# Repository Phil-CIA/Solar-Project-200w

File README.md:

# Solar Project 200W

Solar Project 200W is a prototype-first hardware and firmware effort for a 200W-class solar charging system built around a 4S LiFePO4 battery domain.

## What this repository is for

- Designing and validating a safe MPPT charger path
- Defining control, telemetry, and protection behavior
- Tracking design decisions, handoffs, and bring-up evidence

## Rev2 preparation

Phil selected **retain LM51772 for Rev2**. Open `hardware\kicad\solar-project\Solar Project Rev2.kicad_pro` for new Rev2 work; its schematic/PCB are a metadata-only copy of the reconciled Rev1 development source at `32243b5` (tag `rev2-development-baseline-2026-11-09`), not an implemented or qualified redesign and not for fabrication. See the [revision index](hardware/kicad/solar-project/REVISION-INDEX.md), [consolidation/change register](docs/rev-two-consolidation.md), and current [handoff](HANDOFF.md) for source identity, bench evidence and unresolved work. The controller-comparison requirement in [#20](https://github.com/Phil-CIA/Solar-Project-200w/issues/20) remains open; no BQ25756 evaluation or purchase is requested.

## Rev 1 manufactured baseline

- Only Rev 0 and Rev 1 have been manufactured; Rev 2 is a copied development starting set. Rev 1 is the current production revision. The production release at `C:\Users\user\OneDrive\JLCPCB files\Solar Charger\Rev 1` is authoritative for board identity, manufacturing and board-specific tests. Repository copies support continued development; the schematic, project and BOM differences are described in the board notes.
- Rev 1 is assembled; the supplied manufacturing package and both-side photos are recorded in [board notes](docs/rev-one-board-notes.md).
- Retain the Rev 1 [development tracker](https://github.com/Phil-CIA/Solar-Project-200w/issues/1) and [working plan](docs/rev-one-closure-plan-2026-09-16.md#6-assembled-board-execution-and-issue-1-closure) as qualification references. Later bench findings and current next steps are linked from the handoff; old unpowered checkpoints are not the current board state.
- This is a hobby prototype: keep useful notes and relevant checks, not a formal lab dossier. Assembly does not establish working charging or full-power performance.
- Rev 1 STM32G473 bring-up firmware through `ff89791` is already on `main`; see [firmware notes](firmware/README.md). That is development progress, not proof of board compatibility or a passing powered test.

## System baseline

- PV class: 2x100W panels in parallel (DEC-051)
- Battery class: 12.8V LiFePO4 (4S)
- Rev 1 design targets: 125 W continuous output, 150 W maximum PV operating power, 8-10 A nominal charging, approximately 12 A hardware protection pending verification

## Project structure

- [docs/](docs/): requirements, architecture, decisions, test plans, phase reviews
- [hardware/](hardware/): KiCad files, MPPT notes, wiring maps, implementation checklists
- [firmware/](firmware/): firmware workspace and bring-up software notes

## Start here

1. [HANDOFF.md](HANDOFF.md) - current checkpoint and next step
2. [docs/rev-one-board-notes.md](docs/rev-one-board-notes.md) - working board baseline and known differences
3. [docs/README.md](docs/README.md) - engineering references
4. [docs/decisions-log.md](docs/decisions-log.md) - retained design decisions
5. [SOLAR_HANDOFF_2026-09-19.md](SOLAR_HANDOFF_2026-09-19.md) and [SOLAR_HANDOFF_2026-09-18.md](SOLAR_HANDOFF_2026-09-18.md) for the historical Rev 1 fabrication closeout
6. [hardware/kicad/solar-project/REVISION-INDEX.md](hardware/kicad/solar-project/REVISION-INDEX.md) for KiCad source-of-truth rules

## Simulation workflow

The PV switch gate-drive concept should be verified with SPICE as part of the normal review loop. The project-local LTspice assets are in [hardware/kicad/solar-project/spice](hardware/kicad/solar-project/spice), including the schematic draft [hardware/kicad/solar-project/spice/pv_switch_gate_drive.asc](hardware/kicad/solar-project/spice/pv_switch_gate_drive.asc) and the launcher [hardware/kicad/solar-project/spice/run_ltspice_pv_gate_drive.cmd](hardware/kicad/solar-project/spice/run_ltspice_pv_gate_drive.cmd).

A provisional LTspice integration harness is also present at [hardware/kicad/solar-project/spice/90_system_integration_harness_ltspice.cir](hardware/kicad/solar-project/spice/90_system_integration_harness_ltspice.cir). It is a simplified, staged model of the PV input, buck power stage, and battery boundary. The current run converged to about 13.64 V at the output node and 13.98 V at the battery bus at 4 ms, which is consistent with a basic charging path but still not hardware-validated.

Earlier simulation identified a gate-drive margin problem in the arrangement it modeled. That historical result is not a measured failure of the assembled Rev 1 U14/Q5/Q6 protection circuit; confirm the topology against the Rev 1 production release and use matching low-energy checks before drawing that conclusion.

## Safety notice

This project includes high-current DC power electronics and planned AC-domain integration.
Use staged, current-limited bring-up and treat all safety checks as mandatory gates.

## Session continuity

- [HANDOFF.md](HANDOFF.md)
- [NEXT_CHAT_PROMPT.md](NEXT_CHAT_PROMPT.md)

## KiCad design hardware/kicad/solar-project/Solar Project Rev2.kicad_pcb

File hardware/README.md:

# Hardware

Store hardware development assets here.

Suggested structure:
- `schematics/`
- `pcb/`
- `bom/`
- `manufacturing/`
- `validation/`

Add tool/version notes and board revision history as the project evolves.

## Phase 1 Kickoff Artifacts

- `mppt/block-diagram.md`
- `mppt/schematic-exploration-checklist.md`
- `mppt/interface-assumptions.md`
- `mppt/schematic-notes.md`
- `mppt/net-plan.md`
- `mppt/component-shortlist-template.md`
- `mppt/kicad-implementation-checklist.md`
- `mppt/envelope-decision-worksheet.md`
- `mppt/decision-update-template.md`
- `mppt/buck-topology-notes.md`
- `mppt/github-reference-notes.md`
- `mppt/buck-symbol-placement-checklist.md`
- `mppt/pv-input-stage.md`
- `mppt/pv-input-wiring-map.md`
- `mppt/buck-power-stage-wiring-map.md`
- `mppt/sheet2-component-picks.md`

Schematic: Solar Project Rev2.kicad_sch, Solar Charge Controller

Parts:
10mm1, 10mm2: 10mm LOGO
C1, C8, C12, C22, C28, C33, C44, C45, C46, C47, C48, C51, C54, C57, C58, C59, C60: 100nF; C_0805; Voltage Rated 100V; Tolerance ±10%; Part CL21B104KCFNNNE; LCSC C28233
C2, C55, C56: 1uF; C_0805; Voltage Rated 50V; Tolerance ±10%; Part CL21B105KBFNNNE; LCSC C28323
C3: 100uF; CP_Radial_D6.3mm_P2.50mm; LCSC C49232871
C7: 2.2uF; C_1206; Voltage Rated 100V; Tolerance ±10%; Part CC1206KKX7R0BB225; LCSC C577211
C9, C13: 2.2nF; C_0805; Voltage Rated 50V; Tolerance ±5%; Part CL21C222JBFNNNE; LCSC C28260
C10: 47pF; C_0805; Voltage Rated 50V; Tolerance ±5%; Part CL21C470JBANNNC; LCSC C14857
C14, C53: 100uF; C_1206; Voltage Rated 6.3V; Tolerance ±20%; Part CL31A107MQHNNNE; JLCPCB ID C45783
C15, C34, C35: 2.2uF; C_1206; Voltage Rated 50V; Tolerance ±10%; Part CL31B225KBHNNNE; LCSC C50254
C18: 560uF; CP_Elec_10x12.6; LCSC C264031
C19, C21, C30, C31: 47uF; CP_Radial_D8.0mm_P3.50mm; LCSC C44606514
C20: 180pF; C_0805; LCSC C1794
C23: 100nF; C_0805; LCSC C28233
C24: 22nF; C_0805; LCSC C1710
C25: 1.5nF; C_0805; LCSC C1590
C26: 33nF; C_0805; LCSC C1738
C27, C29: 22uF; C_0805; Voltage Rated 25V; Tolerance ±20%; Part CL21A226MAQNNNE; LCSC C45783
C49, C50: 33pF; C_0805; Voltage Rated 50V; Tolerance ±5%; Part CC0805JRNPO9BN330; LCSC C1798
C52: 220nF; C_0805; Voltage Rated 50V; Tolerance ±10%; Part CL21B224KBFNNNE; LCSC C5378
C61: DNP; C_0805; Voltage Rated 100V; Tolerance ±10%; Part CL21B104KCFNNNE; not fitted
D1, D5: 1SMA4742A; D_DO-214AC(SMA); Part 1SMA4742A; LCSC C19077480
D2: SMBJ48CA; D_SMB; Part SMBJ48CA; LCSC C151264
D3: USBLC6-2SC6; SOT-23-6; MPN USBLC6-2SC6; Digi-Key_PN 497-5235-1-ND
D4, D6, D7, D10: 1N5819WS; D_SOD-323; Forward Voltage (Vf@If) 600mV@1A; Reverse Voltage (Vr) 40V; Part 1N5819WS; LCSC C191023
D8, D11: WS2812B; LED-SMD_4P-L1.6-W1.5_XL-1615RGBC-WS2812B; LCSC C5349954
D9: Green; D_0805; Forward Voltage (VF) 1.6V~2.6V; Part KT-0805G; LCSC C2297
D12: Yellow; D_0805; Forward Voltage (VF) 1.6V~2.6V; Part KT-0805Y; LCSC C2296
F1, F2: 3522-2; Automotive fuse holder keystone 3522-2_KEY; Part - USA Keystone 3522-2, sourced via Digikey/Mo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
J1, J3: Screw_Terminal_01x02; TerminalBlock_Phoenix_MKDS-1,5-2-5.08_1x02_P5.08mm_Horizont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; LCSC C8439
J2: USB4105-GF-A; GCT_USB4105-GF-A; PARTREV B4; LCSC C3020560
J4: Conn_01x04; PinHeader_1x04_P2.54mm_Vertical_SMD_Pin1Right; LCSC C41417361
J7: Fan; PinHeader_1x03_P2.54mm_Vertical; LCSC C29275
J8: Conn_01x04; PinHeader_1x04_P2.54mm_Vertical
L2: L; L_APV_APH1240; LCSC C49308530
L3: L; L_KOHERelec_MDA7030; LCSC C49333024
M1, M2, M3, M4: CSD18540Q5B; TDSON-8-1; LCSC C86513
Q2, Q3, Q7: 2N7002K; Q_SOT-23; Part 2N7002K; LCSC C22379475
Q4: HSBA0119; PQFN-8-EP_6x5mm_P1.27mm_Generic; LCSC C53244070
Q5, Q6: BSC040N10NS5; TDSON-8-1; LCSC C534334
R1, R2, R32, R38, R67: 100kΩ; R_0805; Overload Voltage (Max) 150V; Tolerance ±1%; Part 0805W8F1003T5E; LCSC C17416
R3, R18: 76.8k; R_0805; LCSC C3000581
R4, R26, R27, R41, R65, R69, R70, R71, R72, R73: 10Ω; R_0805; Overload Voltage (Max) 150V; Tolerance ±1%; Part 0805W8F100JT5E; LCSC C17414
R5, R44, R45: 4.7kΩ; R_0805; Overload Voltage (Max) 150V; Tolerance ±1%; Part 0805W8F4701T5E; LCSC C17673
R6, R19, R34, R36, R47, R48, R53, R54, R55, R56, R57, R58, R59, R82, R86: 10kΩ; R_0805; Overload Voltage (Max) 150V; Tolerance ±1%; Part 0805W8F1002T5E; LCSC C17415
R7, R10, R61: 20kΩ; R_0805; Overload Voltage (Max) 150V; Tolerance ±1%; Part 0805W8F2002T5E; LCSC C17523
R8: 27kΩ; R_0805; Overload Voltage (Max) 150V; Tolerance ±1%; Part 0805W8F2702T5E; LCSC C17547
R9: 180k; R_0805; LCSC C17497
R11, R39: 330Ω; R_0805; Overload Voltage (Max) 150V; Tolerance ±1%; Part 0805W8F3300T5E; LCSC C17650
R12: 6.8kΩ; R_0805; Overload Voltage (Max) 150V; Tolerance ±1%; Part 0805W8F6801T5E; LCSC C17730
R13: 1MΩ; R_0805; Overload Voltage (Max) 150V; Tolerance ±1%; Part 0805W8F1004T5E; LCSC C17514
R14: 330kΩ; R_0805; Overload Voltage (Max) 150V; Tolerance ±1%; Part 0805W8F3303T5E; LCSC C17651
R15: 2kΩ; R_0805; Overload Voltage (Max) 150V; Tolerance ±1%; Part 0805W8F2001T5E; LCSC C17537
R16, R22, R80: .005; RES_2012_SUS- wide 0805; LCSC C2073455
R17, R25: 5.62k; R_0805; LCSC C2933470
R20: 499k; R_0805; LCSC C119857
R21: 102k; R_0805; LCSC C119830
R23: 75kΩ; R_0805; Overload Voltage (Max) 150V; Tolerance ±1%; Part 0805W8F7502T5E; LCSC C17743
R24, R62: 5.1kΩ; R_0805; Overload Voltage (Max) 150V; Tolerance ±1%; Part 0805W8F5101T5E; LCSC C17700
R28: 51.7k; R_0805; LCSC C119851
R29: 20.5k; R_0805; LCSC C119842
R30: 40.2k; R_0805; LCSC C119848
R31: 2.43k; R_0805; LCSC C119853
R33, R49, R63, R64: 0Ω; R_0805; Overload Voltage (Max) 150V; Tolerance ±1%; Part 0805W8F0000T5E; LCSC C17888
R35, R81: 180kΩ; R_0805; Overload Voltage (Max) 150V; Tolerance ±1%; Part 0805W8F1803T5E; LCSC C17497
R37, R66: 2.2MΩ; R_0805; Overload Voltage (Max) 150V; Tolerance ±1%; Part 0805W8F2204T5E; LCSC C17539
R40, R43, R74: 100kΩ; R_0805; Overload Voltage (Max) 150V; Tolerance ±1%; Part Number RC0603FR-07100KL; JLCPCB ID C25803
R42, R52, R83, R84, R85: 1kΩ; R_0805; Overload Voltage (Max) 150V; Tolerance ±1%; Part 0805W8F1001T5E; LCSC C17513
R46: 82kΩ; R_0805; Overload Voltage (Max) 150V; Tolerance ±1%; Part 0805W8F8202T5E; LCSC C17840
R50: 10kΩ; R_0805; Overload Voltage (Max) 150V; Tolerance ±1%; Part 0805W8F1002T5E; LCSC C17415; not fitted
R51: 2.7kΩ; R_0805; Overload Voltage (Max) 150V; Tolerance ±1%; Part 0805W8F2701T5E; LCSC C17546
R60: 1.5kΩ; R_0805; Overload Voltage (Max) 150V; Tolerance ±1%; Part 0805W8F1501T5E; LCSC C17515
R68: 1.3k; R_0805; LCSC C2933303
R75: .005; R_0508_1220Metric; LCSC C2073455
R76, R77: .010Ω; RES_2012_SUS- wide 0805
R78, R79: 0.001Ω; R_2512 Shunt 4 pad resistor; LCSC C41382682
S1: Tactile Button, 160gf; SW_TS-1088-AR02016; Voltage Rating (Dc) 12V; Part TS-1088-AR02016; LCSC C720477
SW1, SW2, SW3, SW4, SW5: Tactile Button, 160gf; SW-SMD_4P-L5.1-W5.1-P3.70-LS6.5-TL-2; Voltage Rating (Dc) 12V; Part TS-1187A-B-A-B; LCSC C318884
TP1: TestPoint_Small; PinHeader_1x01_P2.54mm_Vertical; not fitted
TP15, TP16, TP17, TP18: 5015; TestPoint_Keystone_5015_Micro_Mini; PARTREV F
U1: STM32G431CBU6; QFN-48-1EP_7x7mm_P0.5mm_EP5.6x5.6mm; PARTREV 6
U2: ESP32_C3_mini; ESP32 C3 mini; PARTREV 23/05/2022
U3: CP2102-GMR; WQFN-28_L5.0-W5.0-P0.50-BL-EP3.2; Supply Voltage 3V~3.6V; Part CP2102-GMR; LCSC C6568
U4: LM5163; Texas_R-PDSO-G8_EP2.95x4.9mm_Mask2.4x3.1mm_ThermalVias; LCSC C2873264
U5: LP5912-3.3DRV; WSON-6-1EP_2x2mm_P0.65mm_EP1x1.6mm_ThermalVias; LCSC C114569
U6: LM51772QRHARQ1; VFQFN-40-1EP_6x6mm; LCSC C41383743
U7: AHT20; Humidity sensor; PARTREV V1.0; LCSC C2757850
U8: SSD1306_OLED; 0.96 inOLED display SSD1306; LCSC C5248080
U9: LMV393; SOIC-8-1EP_3.9x4.9mm_P1.27mm_EP2.29x3mm_ThermalVias; LCSC C7984
U10, U11, U12: INA241A3IDDFR; TSOT-23-8; LCSC C129346
U14: LM74502HDDFR; Texas_DDF0008A_SOT-8_1.6x2.9mm_P0.65mm; LCSC C5219202
X2: X49SM8MSD2SC; CRYSTAL-SMD_L11.5-W4.8-LS12.7; Frequency Tolerance ±20ppm; Part X49SM8MSD2SC; LCSC C12674

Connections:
BAT_BUS_POS: D4.2, F2.1, F2.2, R20.1, R78.3, R78.4, R79.3, R79.4, U11.8 (+)
BAT_PACK_POS: J3.2, R78.1, R78.2, R79.1, R79.2, U11.1 (-)
BTN_DN_N: SW2.1 (A), U1.41 (PB3)
BTN_ENT_N: SW5.1 (A), U1.47 (PB9)
BTN_LT_N: SW4.1 (A), U1.42 (PB4)
BTN_RT_N: SW3.1 (A), U1.39 (PC10)
BTN_UP_N: SW1.1 (A), U1.38 (PA15)
CHG_OUT_POS: D6.2, F2.3, F2.4, J7.3, Q6.5 (D), R81.1, U6.18 (VOUT)
CSB_2: L2.1, R22.2, R27.1, R75.2
CTRL_3V3: C12.1, C44.1, C48.1, C53.1, C54.1, C55.1, J8.3, R5.2, R19.1, R21.1, R34.1, R39.1, R51.1, R53.1, R54.1, R55.1, R56.1, R57.1, R58.1, R59.1, R74.1, TP17.1, U1.1 (VBAT), U1.20 (VREF+), U1.21 (VDDA), U1.23 (VDD), U1.35 (VDD), U1.48 (VDD), U3.6 (VDD), U5.1 (OUT), U6.38 (RST), U7.2 (VDD), U8.2 (VCC), U9.8 (V+), U11.7 (REF1)
CTRL_5V: C9.1, C14.1, C51.2, C56.1, C57.1, D8.2 (VDD), D10.1, D11.2 (VDD), L3.2, R10.2, R11.1, TP18.1, U2.16 (5V), U5.4 (EN), U5.6 (IN), U10.6 (V+), U11.6 (V+), U12.6 (V+)
CTRL_EN_CHG: R73.1, U1.25 (PB12)
CTS: U1.14 (PA6), U3.23 (CTS)
CTS_ESP: U1.22 (PB10), U2.7 (GPIO20)
FAN_TACH: J7.2, U1.43 (PB5)
FAULT_OCP: R53.2, U1.17 (PB0), U9.7
FAULT_OVP: R19.2, U1.18 (PB1), U9.1
Fan Control: R4.1, U1.40 (PC11)
HO1: M1.4 (G), R69.1
HO2: M4.4 (G), R71.1
I2C CLK: J8.1, R44.1, U1.45 (PB7), U6.6 (SCL_CFG4), U7.3 (SCL), U8.3 (SLC)
I2C DATA: J8.4, R45.1, U1.44 (PB6), U6.5 (SDA_CFG3), U7.4 (SDA), U8.4 (SDA)
LO1: M2.4 (G), R70.1
LO2: M3.4 (G), R72.1
unnamed: C9.2, C10.1, R12.2
unnamed: C24.1, R31.1
unnamed: D8.4 (DIN), U1.19 (PB2)
unnamed: D9.2, R11.2
unnamed: D8.1 (DOUT), D11.4 (DIN)
unnamed: D12.2, R39.2
unnamed: F1.3, F1.4, J1.1
unnamed: J2.A5 (CC1), R24.2
unnamed: J2.B5 (CC2), R62.2
unnamed: D3.3 (I/O2), J2.A7 (DN1), J2.B7 (DN2)
unnamed: D3.1 (I/O1), J2.A6 (DP1), J2.B6 (DP2)
unnamed: J2.A8 (SBU1), J2.B8 (SBU2)
unnamed: J7.1, Q3.3 (D)
unnamed: Q2.3 (D), R42.1, R43.2
unnamed: Q2.1 (G), R40.2, R41.2
unnamed: Q3.1 (G), R1.1, R4.2
unnamed: D1.2, Q4.4 (G), R42.2
unnamed: D5.2, Q5.4 (G), Q6.4 (G), R2.2, R65.2
unnamed: Q7.1 (G), R73.2, R74.2
unnamed: R7.2, R10.1
unnamed: R9.1, R12.1
unnamed: R14.2, R15.1
unnamed: R37.2, R66.1
unnamed: R46.1, R68.1
unnamed: R60.1, R61.2
unnamed: R84.1, U12.5
unnamed: R85.1, U11.5
unnamed: C47.1, R59.2, S1.1 (A), U1.7 (PG10-~RST)
unnamed: R54.2, SW1.2 (B)
unnamed: R55.2, SW2.2 (B)
unnamed: R56.2, SW3.2 (B)
unnamed: R57.2, SW4.2 (B)
unnamed: R58.2, SW5.2 (B)
unnamed: R86.1, U1.46 (PB8-BOOT0)
unnamed: C50.1, U1.5 (PF0-OSC_IN), X2.1
unnamed: C49.1, U1.6 (PF1-OSC_OUT), X2.2
unnamed: D3.6 (I/O1), U3.4 (D+)
unnamed: D3.4 (I/O2), U3.5 (D-)
unnamed: R5.1, U3.9 (RST#)
unnamed: C13.2, U4.7 (BST)
unnamed: R13.2, R14.1, U4.3 (EN/UVLO)
unnamed: C10.2, R6.2, R7.1, U4.5 (FB)
unnamed: R8.1, U4.4 (RON)
unnamed: C13.1, L3.1, R9.2, U4.8 (SW)
unnamed: C15.1, D4.1, D6.1, D7.1, R13.1, U4.2 (VIN)
unnamed: R33.1, U6.9 (ADDR_SLOPE_CFG1)
unnamed: R30.1, U6.10 (CDC)
unnamed: R29.1, U6.8 (CFG2)
unnamed: C24.2, C25.2, U6.13 (COMP)
unnamed: C20.1, C61.1, R26.2, U6.22 (CSA)
unnamed: C20.2, C61.2, R27.2, U6.21 (CSB)
unnamed: C22.1, U6.25 (HB1)
unnamed: C23.1, U6.31 (HB2)
unnamed: R69.2, U6.24 (HO1)
unnamed: R71.2, U6.32 (HO2)
unnamed: R68.2, U6.16 (ILIMCOMP_ISET)
unnamed: R63.1, U6.19 (ISNSN)
unnamed: R64.1, U6.20 (ISNSP)
unnamed: R70.2, U6.27 (LO1)
unnamed: R72.2, U6.30 (LO2)
unnamed: R32.2, U6.7 (MODE)
unnamed: R28.1, U6.12 (RT)
unnamed: C26.2, U6.2 (SS_ATRK)
unnamed: C27.1, C46.1, U6.1 (VCC1)
unnamed: U7.1 (NC), U7.6 (NC)
unnamed: R65.1, U14.6 (GATE)
unnamed: R66.2, R67.1, U14.7 (OV)
unnamed: C52.2, U14.4 (VCAP)
OCP_MEAS: R49.1, R83.1, U10.5
OCP_REF: R51.2, R52.1, U9.6 (-)
OCP_SENSE: R49.2, R50.1, U9.5 (+)
OVP_REF: R21.2, R48.1, U9.2 (-)
OVP_SENSE: R20.2, R47.1, U9.3 (+)
PA0: C58.1, R83.2, U1.8 (PA0)
PA1: C59.1, R84.2, U1.9 (PA1)
PC4: C60.1, R85.2, U1.16 (PC4)
PV_FUSED_POS: D2.2, F1.1, F1.2, R35.1, R76.1, R77.1, U12.8 (+)
PV_IN_POS: C7.1, C8.1, C19.1, C21.1, C28.1, C30.1, C31.1, M1.5 (D), Q4.5 (D), R18.1, R23.1, TP16.1, U6.36 (VIN), U6.40 (BIAS)
PV_Q4_SOURCE: D1.1, Q4.1 (S), Q4.2 (S), Q4.3 (S), R43.1, R76.2, R77.2, U12.1 (-)
PWR_NEG: C1.2, C2.2, C3.2, C7.2, C8.2, C12.2, C14.2, C15.2, C18.2, C19.2, C21.2, C25.1, C26.1, C27.2, C28.2, C29.2, C30.2, C31.2, C33.1, C34.2, C35.2, C44.2, C45.2, C46.2, C47.2, C48.2, C49.2, C50.2, C51.1, C53.2, C54.2, C55.2, C56.2, C57.2, C58.2, C59.2, C60.2, D2.1, D3.2 (GND), D8.3 (GND), D9.1, D11.3 (GND), D12.1, J1.2, J2.A1_B12 (GND), J2.B1_A12 (GND__1), J2.SH1 (SHELL_GND), J2.SH2 (SHELL_GND__1), J2.SH3 (SHELL_GND__2), J2.SH4 (SHELL_GND__3), J3.1, J4.4, J8.2, M2.1 (S), M2.2 (S), M2.3 (S), M3.1 (S), M3.2 (S), M3.3 (S), Q2.2 (S), Q3.2 (S), Q7.2 (S), R1.2, R6.1, R8.2, R15.2, R17.2, R24.1, R25.2, R28.2, R29.2, R30.2, R31.2, R33.2, R36.2, R38.2, R40.1, R44.2, R45.2, R46.2, R47.2, R48.2, R50.2, R52.2, R60.2, R62.1, R67.2, R82.2, R86.2, S1.2 (B), SW1.3 (C), SW1.4 (D), SW2.3 (C), SW2.4 (D), SW3.3 (C), SW3.4 (D), SW4.3 (C), SW4.4 (D), SW5.3 (C), SW5.4 (D), TP15.1, U1.49 (VSS), U2.15 (GND), U3.3 (GND), U4.1 (GND), U4.9 (TH_pd), U5.5 (GND), U5.7 (EP), U6.3 (SYNC), U6.4 (DTRK), U6.17 (AGND), U6.28 (PGND), U6.41 (GND), U7.5 (GND), U8.1 (GND), U8.5 (GND), U8.6 (GND), U8.7 (GND), U8.8 (GND), U9.4 (V-), U9.9 (EP), U10.2 (GND), U10.3 (REF2), U10.4 (GND), U10.7 (REF1), U11.2 (GND), U11.3 (REF2), U11.4 (GND), U12.2 (GND), U12.3 (REF2), U12.4 (GND), U12.7 (REF1), U14.2 (GND)
RTS: U1.15 (PA7), U3.24 (RTS)
RTS_ESP: U1.24 (PB11), U2.8 (GPIO21)
RXD: U1.31 (PA9), U3.25 (RXD)
RXD_ESP: U1.33 (PA11), U2.9 (GPIO0)
SRC: D5.1, Q5.1 (S), Q5.2 (S), Q5.3 (S), Q6.1 (S), Q6.2 (S), Q6.3 (S), R2.1, U14.8 (SRC)
SWCLK: J4.1, U1.37 (PA14)
SWDIO: J4.2, U1.36 (PA13)
SW_1: C22.2, M1.1 (S), M1.2 (S), M1.3 (S), M2.5 (D), R22.1, R26.1, R75.1, U6.23 (SW1)
SW_2: C23.2, L2.2, M3.5 (D), M4.1 (S), M4.2 (S), M4.3 (S), U6.33 (SW2)
TXD: U1.32 (PA10), U3.26 (TXD)
TXD_ESP: U1.34 (PA12), U2.10 (GPIO1)
U6_FLT: R34.2, U1.2 (PC13), U6.11 (FLT)
U6_VCC2: C29.1, C45.1, R32.1, U6.29 (VCC2)
VBUS: C1.1, C2.1, D3.5 (VBUS), D7.2, D10.2, J2.A4_B9 (VBUS), J2.B4_A9 (VBUS__1), U3.7 (REGIN), U3.8 (VBUS)
V_in_ADC: R35.2, R36.1, U1.12 (PA4)
V_in_FB: R17.1, R18.2, U6.15 (VIN-FB)
V_in_ON: R41.1, U1.13 (PA5)
V_out: C3.1, C18.1, C33.2, C34.1, C35.1, M4.5 (D), R3.1, R16.1, R64.2, R80.1, U10.8 (+)
V_out _on: R38.1, U1.30 (PA8), U14.1 (EN_UVLO)
V_out_ADC: R81.2, R82.1
V_out_SNS_N: C52.1, Q5.5 (D), R16.2, R37.1, R63.2, R80.2, TP1.1 (1_1), U10.1 (-), U14.5 (VS)
_OUTPUT Feedback: R3.2, R25.1, U6.14 (FB_INT)
_Undervoltage Feedback: Q7.3 (D), R23.2, R61.1, U6.37 (EN_UVLO)

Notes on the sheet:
Nav Buttons
zone A
5 Volt Buck
OLED Display
Output Protection
Zone C
DEbugging conn
WiFi
Fan Control
Temp and Humidity sensor Board

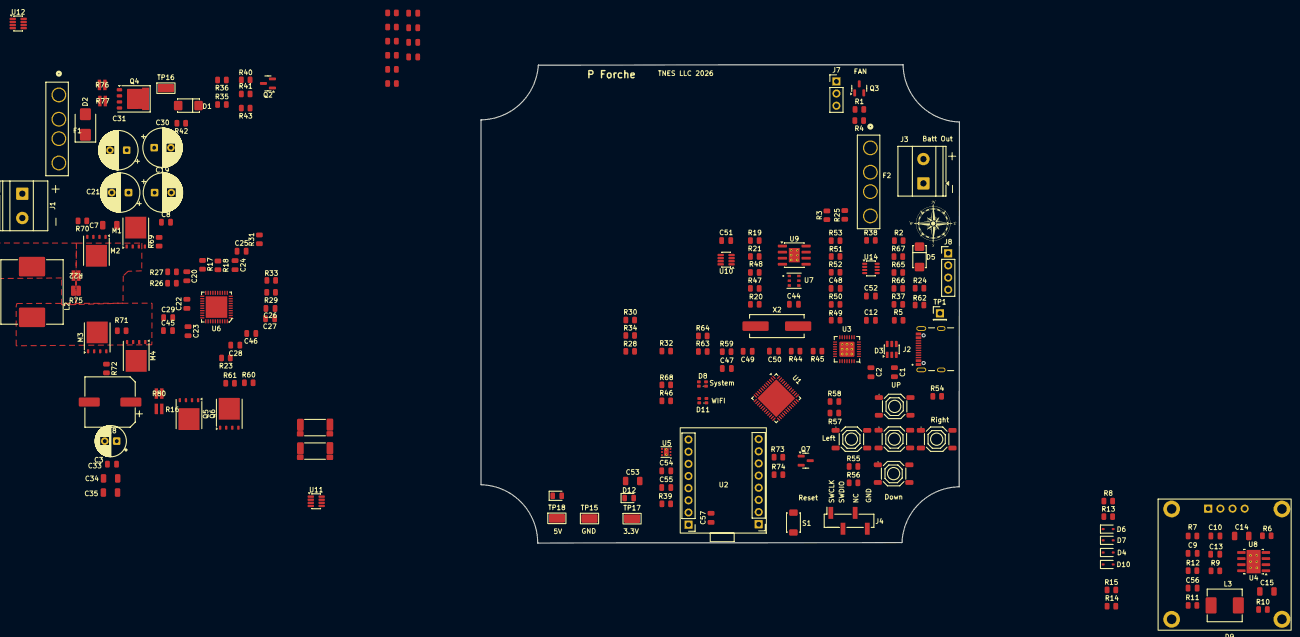
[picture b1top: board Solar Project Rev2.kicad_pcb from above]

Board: 4 copper layers, 100.0 x 99.9 mm, 191 parts (1 on the bottom side), 127 nets, no tracks yet.

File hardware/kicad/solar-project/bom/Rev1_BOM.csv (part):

Item #,Designator,Qty,Value,Footprint,LCSC Part #,Description
1,"10mm1, 10mm2",2,,1My_Parts_ Passive:10mm LOGO,,
2,"C1, C8, C12, C22, C28, C33, C44, C45, C46, C47, C48, C51, C52, C54, C57",15,100nF,PCM_JLCPCB:C_0805,C28233,100V 100nF X7R ±10% 0805 Multilayer Ceramic Capacitors MLCC - SMD/SMT ROHS
3,"C2, C55, C56",3,1uF,PCM_JLCPCB:C_0805,C28323,50V 1uF X7R ±10% 0805 Multilayer Ceramic Capacitors MLCC - SMD/SMT ROHS
4,C3,1,100uF,Capacitor_THT:CP_Radial_D6.3mm_P2.50mm,C49232871,Unpolarized capacitor
5,"C7, C15, C34, C35",4,2.2uF,PCM_JLCPCB:C_1206,C50254,50V 2.2uF X7R ±10% 1206 Multilayer Ceramic Capacitors MLCC - SMD/SMT ROHS
6,"C9, C13",2,2.2nF,PCM_JLCPCB:C_0805,C28260,50V 2.2nF C0G ±5% 0805 Multilayer Ceramic Capacitors MLCC - SMD/SMT ROHS
7,C10,1,47pF,PCM_JLCPCB:C_0805,C14857,50V 47pF C0G ±5% 0805 Multilayer Ceramic Capacitors MLCC - SMD/SMT ROHS
8,"C14, C53",2,100uF,PCM_JLCPCB:C_1206,C15008,6.3V 100uF X5R ±20% 1206 Multilayer Ceramic Capacitors MLCC - SMD/SMT ROHS
9,C18,1,560uF,Capacitor_SMD:CP_Elec_10x12.6,C264031,Unpolarized capacitor
10,"C19, C21, C30",3,47uF,Capacitor_THT:C_Radial_D8.0mm_H7.0mm_P3.50mm,C44606514,Unpolarized capacitor
11,C20,1,180pF,PCM_JLCPCB:C_0805,C1794,Unpolarized capacitor
12,C23,1,100nF,PCM_JLCPCB:C_0805,C28233,Unpolarized capacitor
13,C24,1,22nF,PCM_JLCPCB:C_0805,C1710,Unpolarized capacitor
14,C25,1,1.5nF,PCM_JLCPCB:C_0805,C1590,Unpolarized capacitor
15,C26,1,33nF,PCM_JLCPCB:C_0805,C1738,Unpolarized capacitor
16,"C27, C29",2,22uF,PCM_JLCPCB:C_0805,C45783,25V 22uF X5R ±20% 0805 Multilayer Ceramic Capacitors MLCC - SMD/SMT ROHS
17,C31,1,47uF,Capacitor_THT:CP_Radial_D8.0mm_P3.50mm,C44606514,Unpolarized capacitor
18,"C49, C50",2,33pF,PCM_JLCPCB:C_0805,C1798,50V 33pF NP0 ±5% 0805 Multilayer Ceramic Capacitors MLCC - SMD/SMT ROHS
19,"D1, D5",2,1SMA4742A,PCM_JLCPCB:D_DO-214AC(SMA),C19077480,Independent Type 11.4V~12.6V 1W 12V SMA(DO-214AC) Zener Diodes ROHS
20,D2,1,SMBJ60CA,PCM_JLCPCB:D_SMB,C19077593,6.2A 600W 96.8V 73.7V Bidirectional 60V SMB ESD and Surge Protection (TVS/ESD) ROHS
21,D3,1,USBLC6-2SC6,Package_TO_SOT_SMD:SOT-23-6,C7519,"Very low capacitance ESD protection diode, 2 data-line, SOT-23-6"
22,"D4, D6, D7, D10",4,1N5819WS,PCM_JLCPCB:D_SOD-323,C191023,40V 600mV@1A 1A SOD-323 Schottky Diodes ROHS
23,D8,1,WS2812B,PCM_JLCPCB:LED-SMD_4P-L1.6-W1.5_XL-1615RGBC-WS2812B,C5349954,1615 RGB LEDs(Built-in IC) ROHS
24,D9,1,Green,PCM_JLCPCB:D_0805,C2297,Emerald 0805 LED Indication - Discrete ROHS
25,D12,1,Yellow,PCM_JLCPCB:D_0805,C2296,Yellow 0805 LED Indication - Discrete ROHS
26,"F1, F2",2,Fuse,Fuse:Fuseholder_Littelfuse_100_series_5x25mm,C142864,Fuse
27,"J1, J3",2,Screw_Terminal_01x02,"TerminalBlock_Phoenix:TerminalBlock_Phoenix_MKDS-1,5-2-5.08_1x02_P5.08mm_Horizontal",C8439,"Generic screw terminal, single row, 01x02, script generated (kicad-library-utils/schlib/autogen/connector/)"
28,J2,1,USB4105-GF-A,1My_Parts_ Connectors:GCT_USB4105-GF-A,C3020560,
29,J4,1,Conn_01x04,Connector_PinHeader_2.54mm:PinHeader_1x04_P2.54mm_Vertical_SMD_Pin1Right,C41417361,"Generic connector, single row, 01x04, script generated (kicad-library-utils/schlib/autogen/connector/)"
30,J5,1,Conn_01x03_Socket,Connector_PinHeader_2.54mm:PinHeader_1x03_P2.54mm_Vertical,C2937625,"Generic connector, single row, 01x03, script generated"
31,J6,1,20021121-00010C4LF,digikey-footprints:PinHeader_2x5_P1.27mm,,
32,L2,1,L,Inductor_SMD:L_APV_APH1240,C49308530,Inductor
33,L3,1,L,Inductor_SMD:L_KOHERelec_MDA7030,C49333024,Inductor
34,"M1, M2, M3, M4",4,CSD18540Q5B,Package_TO_SOT_SMD:TDSON-8-1,C86513,"100A Id, 60V Vds, NexFET N-Channel Power MOSFET, 2.2mOhm Ron, 41nC Qg(typ), SON8 5x6mm"
35,"Q2, Q3, Q7",3,2N7002K,PCM_JLCPCB:Q_SOT-23,C22379475,"60V 340mA 350mW 900mΩ@10V,500mA 2.5V@1mA 1PCSNChannel SOT-23 MOSFETs ROHS"
36,Q4,1,HSBA0119,Package_DFN_QFN:PQFN-8-EP_6x5mm_P1.27mm_Generic,C53244070,P-MOSFET transistor
37,"Q5, Q6",2,BSC040N10NS5,Package_TO_SOT_SMD:TDSON-8-1,C534334,"100A Id, 100V Vds, OptiMOS N-Channel Power MOSFET, 4.0mOhm Ron, Qg (typ) 58.0nC, PG-TDSON-8"
38,"R1, R2, R32, R38, R40, R43, R67, R74",8,100kΩ,PCM_JLCPCB:R_0805,C17416,125mW Thick Film Resistors 150V ±100ppm/°C ±1% 100kΩ 0805 Chip Resistor - Surface Mount ROHS
39,R3,1,76.8k,PCM_JLCPCB:R_0805,C3000581,ResistorRES 76.8kΩ ±1% 125mW 0805
40,"R4, R26, R27, R41, R65, R69, R70, R71, R72, R73",10,10Ω,PCM_JLCPCB:R_0805,C17414,125mW Thick Film Resistors 150V ±1% ±200ppm/°C 10Ω 0805 Chip Resistor - Surface Mount ROHS
41,"R5, R44, R45",3,4.7kΩ,PCM_JLCPCB:R_0805,C17673,125mW Thick Film Resistors 150V ±100ppm/°C ±1% 4.7kΩ 0805 Chip Resistor - Surface Mount ROHS
42,"R6, R19, R34, R36, R47, R48, R50, R53, R54, R55, R56, R57, R58, R59",14,10kΩ,PCM_JLCPCB:R_0805,C17415,125mW Thick Film Resistors 150V ±100ppm/°C ±1% 10kΩ 0805 Chip Resistor - Surface Mount ROHS
43,"R7, R10, R61",3,20kΩ,PCM_JLCPCB:R_0805,C17523,125mW Thick Film Resistors 150V ±100ppm/°C ±1% 20kΩ 0805 Chip Resistor - Surface Mount ROHS
44,R8,1,27kΩ,PCM_JLCPCB:R_0805,C17547,125mW Thick Film Resistors 150V ±100ppm/°C ±1% 27kΩ 0805 Chip Resistor - Surface Mount ROHS
45,R9,1,180k,PCM_JLCPCB:R_0805,C17497,Resistor
46,"R11, R39",2,330Ω,PCM_JLCPCB:R_0805,C17650,125mW Thick Film Resistors 150V ±100ppm/°C ±1% 330Ω 0805 Chip Resistor - Surface Mount ROHS
47,R12,1,6.8kΩ,PCM_JLCPCB:R_0805,C17730,125mW Thick Film Resistors 150V ±100ppm/°C ±1% 6.8kΩ 0805 Chip Resistor - Surface Mount ROHS
48,R13,1,1MΩ,PCM_JLCPCB:R_0805,C17514,125mW Thick Film Resistors 150V ±100ppm/°C ±1% 1MΩ 0805 Chip Resistor - Surface Mount ROHS
49,R14,1,330kΩ,PCM_JLCPCB:R_0805,C17651,125mW Thick Film Resistors 150V ±100ppm/°C ±1% 330kΩ 0805 Chip Resistor - Surface Mount ROHS
50,R15,1,2kΩ,PCM_JLCPCB:R_0805,C17537,125mW Thick Film Resistors 150V ±100ppm/°C ±1% 2kΩ 0805 Chip Resistor - Surface Mount ROHS
51,"R16, R22",2,0.001ohms,Resistor_SMD:R_Shunt_Vishay_WSK2512_6332Metric_T2.66mm,C41382682,Shunt resistor with Kelvin connections
52,R17,1,5.62k,PCM_JLCPCB:R_0805,C2933470,Resistor RES 5.62kΩ ±1% 125mW 0805
53,R18,1,76.8k,PCM_JLCPCB:R_0805,C3000581,Resistor RES 76.8kΩ ±1% 125mW 0805
54,R20,1,499k,PCM_JLCPCB:R_0805,C119857,Resistor
55,R21,1,102k,PCM_JLCPCB:R_0805,C119830,Resistor
56,R23,1,75kΩ,PCM_JLCPCB:R_0805,C17743,125mW Thick Film Resistors 150V ±100ppm/°C ±1% 75kΩ 0805 Chip Resistor - Surface Mount ROHS
57,"R24, R62",2,5.1kΩ,PCM_JLCPCB:R_0805,C17700,125mW Thick Film Resistors 150V ±100ppm/°C ±1% 5.1kΩ 0805 Chip Resistor - Surface Mount ROHS
58,R25,1,5.62k,PCM_JLCPCB:R_0805,C2933470,Resistor  RES 5.62kΩ ±1% 125mW 0805
59,R28,1,51.7k,PCM_JLCPCB:R_0805,C119851,Resistor
60,R29,1,20.5k,PCM_JLCPCB:R_0805,C119842,Resistor
61,R30,1,40.2k,PCM_JLCPCB:R_0805,C119848,Resistor
62,R31,1,2.43k,PCM_JLCPCB:R_0805,C119853,Resistor
63,"R33, R49, R63, R64",4,0Ω,PCM_JLCPCB:R_0805,C17888,125mW Thick Film Resistors 150V ±800ppm/°C ±1% 0Ω 0805 Chip Resistor - Surface Mount ROHS
64,R35,1,180kΩ,PCM_JLCPCB:R_0805,C17497,125mW Thick Film Resistors 150V ±100ppm/°C ±1% 180kΩ 0805 Chip Resistor - Surface Mount ROHS
65,"R37, R66",2,2.2MΩ,PCM_JLCPCB:R_0805,C17539,125mW Thick Film Resistors 150V ±100ppm/°C ±1% 2.2MΩ 0805 Chip Resistor - Surface Mount ROHS
66,"R42, R52",2,1kΩ,PCM_JLCPCB:R_0805,C17513,125mW Thick Film Resistors 150V ±100ppm/°C ±1% 1kΩ 0805 Chip Resistor - Surface Mount ROHS
67,R46,1,82kΩ,PCM_JLCPCB:R_0805,C17840,125mW Thick Film Resistors 150V ±100ppm/°C ±1% 82kΩ 0805 Chip Resistor - Surface Mount ROHS
68,R51,1,2.7kΩ,PCM_JLCPCB:R_0805,C17546,125mW Thick Film Resistors 150V ±100ppm/°C ±1% 2.7kΩ 0805 Chip Resistor - Surface Mount ROHS
69,R60,1,1.5kΩ,PCM_JLCPCB:R_0805,C17515,125mW Thick Film Resistors 150V ±100ppm/°C ±1% 1.5kΩ 0805 Chip Resistor - Surface Mount ROHS
70,R68,1,1.3k,PCM_JLCPCB:R_0805,C2933303,Resistor
71,S1,1,"Tactile Button, 160gf",PCM_JLCPCB:SW_TS-1088-AR02016,C720477,Without 50mA 4mm 100MΩ 100000 Times 12V 160gf 3mm 2mm Round Button Standing paste SPST SMD Tactile Switches ROHS
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
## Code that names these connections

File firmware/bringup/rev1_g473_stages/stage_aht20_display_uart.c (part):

/* Rev 1 stage: PB6/PB7 software I2C + USART1 + PB2 D8/D11 railroad heartbeat. */

#include <stdbool.h>
#include <stdint.h>
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#define USART_RDR REG32(USART1_BASE + 0x24UL)
#define USART_TDR REG32(USART1_BASE + 0x28UL)

/* ESP32-C3 UART0 (GPIO21 U0TXD) arrives on PB11 = USART3_RX (AF7). Receive-only relay:
 * PB10 (to ESP GPIO20 U0RXD) is left in its reset high-Z state so the ESP is never driven. */
#define RCC_APB1ENR1 REG32(RCC_BASE + 0x58UL)
#define USART3_EN_BIT (1UL << 18)
#define USART3_BASE 0x40004800UL
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#define ESPLOG_LINE_MAX 160U
#define ESPLOG_LINES_PER_PUMP 8U

/* PA4 (SENSE_PV_V) is ADC2_IN17 on STM32G473; it is not routed to ADC1. */
#define ADC2_BASE 0x50000100UL
#define ADC12_COMMON_BASE 0x50000300UL
#define ADC_ISR REG32(ADC2_BASE + 0x00UL)
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#define PB2_BIT (1UL << 2) /* WS2812 data for D8->D11 chain */
#define PB2_SET PB2_BIT
#define PB2_CLR (PB2_BIT << 16U)
#define PC13_BIT (1UL << 13) /* U6_FLT (open-drain, pulled up by R34) */
#define PB12_BIT (1UL << 12) /* CTRL_EN_CHG: active-high EN/UVLO clamp */

#define AHT20_ADDR 0x38U
#define OLED_ADDR 0x3CU
#define U6_ADDR 0x6AU
#define WS_RESET_CYCLES (300U * 16U) /* 300 us at 16 MHz */
#define PA5_BIT (1UL << 5) /* V_in_ON */
#define PA8_BIT (1UL << 8) /* V_out _on: U14 EN/UVLO */

#define VIN_ADC_SHUTDOWN_MV 50000U
#define VIN_ADC_SCALE_NUM 190U
#define VIN_ADC_SCALE_DEN 10U
#define BENCH_JUMPER_FITTED 0U /* TP1-to-CHG_OUT_POS jumper removed; U6 TEST controls U14 */
#define ARM_WINDOW_MS 3000U
#define QUIET_TEST_LOG 1U
#define CMD_IDLE_EXECUTE_MS 150U
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    (void)RCC_AHB2ENR;

    GPIO_MODER(GPIOA_BASE) = (GPIO_MODER(GPIOA_BASE) & ~((3UL << (4U * 2U)) | (3UL << (5U * 2U)) | (3UL << (8U * 2U)))) |
                             (3UL << (4U * 2U)) | /* PA4 analog (V_in_ADC) */
                             (1UL << (5U * 2U)) | /* PA5 output (V_in_ON) */
                             (1UL << (8U * 2U));  /* PA8 output (V_out _on) */
    GPIO_BSRR(GPIOA_BASE) = PA5_BIT; /* default ON: active-high control */
    GPIO_BSRR(GPIOA_BASE) = PA8_BIT << 16U; /* default OFF */
}
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    uart_line("  I2C SPEED <kHz>");
    uart_line("  START <ms> (deprecated)");
    uart_line("  STOP");
    uart_line("  ESPLOG ON|OFF  (relay ESP UART0 via PB11; paused while armed/running)");
}

static void print_reg_result(const char *name, uint8_t reg) {
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    uart_line("U6_TEST I2C_IMPL=bitbang (no HAL ErrorCode)");

    {
        /* Write-1-to-clear OC/UV in STATUS_BYTE while PB12 still holds EN/UVLO low (works at idle;
         * the address-only CLEAR_FAULTS write did not clear a latched OC, and clearing during
         * the run wedged I2C). UV stays set at idle because of the clamp. */
        uint8_t pre_78 = 0U;
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
    uart_line("");
    uart_line("Solar Rev1 AHT20/OLED stage");
    uart_line("USART1 115200 8N1 on PA9/PA10");
    uart_write("BUILD ");
    uart_line(BUILD_ID);
    esplog_init();
    uart_line("ESPLOG ON (USART3 RX PB11 <- ESP GPIO21, 115200)");
    uart_line(g_vin_adc_ok ? "VIN ADC init OK" : "VIN ADC init FAIL");

    const bool has_aht20 = aht20_probe();
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                    vin_path_on = false;
                    vin_path_enable(false);
                    if (!vin_cutoff_reported) {
                        uart_line("VIN cutoff: PA5 OFF (>=50V input)");
                        vin_cutoff_reported = true;
                    }
                }
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
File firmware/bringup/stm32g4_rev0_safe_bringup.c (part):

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
#define CTRL_PWM_MAIN_PORT GPIOA
#define CTRL_PWM_MAIN_PIN GPIO_PIN_8
#define CTRL_EN_CHG_PORT GPIOB
#define CTRL_EN_CHG_PIN GPIO_PIN_5
#define LEGACY_V_IN_ON_PORT GPIOA
#define LEGACY_V_IN_ON_PIN GPIO_PIN_5

#define FAULT_OCP_PORT GPIOB
#define FAULT_OCP_PIN GPIO_PIN_0
#define FAULT_OVP_PORT GPIOB
#define FAULT_OVP_PIN GPIO_PIN_1

#define SW_I2C_DATA_PORT GPIOB
#define SW_I2C_DATA_PIN GPIO_PIN_6
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static void safe_outputs(void)
{
    HAL_GPIO_WritePin(CTRL_PWM_MAIN_PORT, CTRL_PWM_MAIN_PIN, GPIO_PIN_RESET);
    HAL_GPIO_WritePin(CTRL_EN_CHG_PORT, CTRL_EN_CHG_PIN, GPIO_PIN_RESET);
    HAL_GPIO_WritePin(LEGACY_V_IN_ON_PORT, LEGACY_V_IN_ON_PIN, GPIO_PIN_RESET);
}

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    print_line("Commands:");
    print_line("  ?            help");
    print_line("  status       print faults and output latch states");
    print_line("  fault        print FAULT_OCP/PB0 and FAULT_OVP/PB1");
    print_line("  adc          print raw PA4/PA6/PA7 ADC values");
    print_line("  i2cscan      software I2C scan on PB6=data, PB7=clock");
    print_line("  pulse en     pulse CTRL_EN_CHG/PB5 for 100 ms");
    print_line("  pulse legacy pulse V_in_ON/PA5 for 100 ms");
    print_line("  pulse pwm    pulse CTRL_PWM_MAIN/PA8 for 10 ms, scope-only");
    print_line("  safe         force all control outputs low");
}

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
    snprintf(line, sizeof(line),
             "STATUS OCP=%u OVP=%u PA8_PWM=%u PB5_EN=%u PA5_LEGACY=%u",
             HAL_GPIO_ReadPin(FAULT_OCP_PORT, FAULT_OCP_PIN) == GPIO_PIN_SET ? 1u : 0u,
             HAL_GPIO_ReadPin(FAULT_OVP_PORT, FAULT_OVP_PIN) == GPIO_PIN_SET ? 1u : 0u,
             HAL_GPIO_ReadPin(CTRL_PWM_MAIN_PORT, CTRL_PWM_MAIN_PIN) == GPIO_PIN_SET ? 1u : 0u,
             HAL_GPIO_ReadPin(CTRL_EN_CHG_PORT, CTRL_EN_CHG_PIN) == GPIO_PIN_SET ? 1u : 0u,
             HAL_GPIO_ReadPin(LEGACY_V_IN_ON_PORT, LEGACY_V_IN_ON_PIN) == GPIO_PIN_SET ? 1u : 0u);
    print_line(line);
}
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    char line[80];

    snprintf(line, sizeof(line), "FAULT OCP=%u OVP=%u",
             HAL_GPIO_ReadPin(FAULT_OCP_PORT, FAULT_OCP_PIN) == GPIO_PIN_SET ? 1u : 0u,
             HAL_GPIO_ReadPin(FAULT_OVP_PORT, FAULT_OVP_PIN) == GPIO_PIN_SET ? 1u : 0u);
    print_line(line);
}

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    } else if (strcmp(command, "i2cscan") == 0) {
        i2c_scan();
    } else if (strcmp(command, "pulse en") == 0) {
        pulse_line(CTRL_EN_CHG_PORT, CTRL_EN_CHG_PIN, 100u);
        print_status();
    } else if (strcmp(command, "pulse legacy") == 0) {
        pulse_line(LEGACY_V_IN_ON_PORT, LEGACY_V_IN_ON_PIN, 100u);
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    __HAL_RCC_GPIOB_CLK_ENABLE();

    HAL_GPIO_WritePin(GPIOA, CTRL_PWM_MAIN_PIN | LEGACY_V_IN_ON_PIN, GPIO_PIN_RESET);
    HAL_GPIO_WritePin(GPIOB, CTRL_EN_CHG_PIN, GPIO_PIN_RESET);
    HAL_GPIO_WritePin(GPIOB, SW_I2C_DATA_PIN | SW_I2C_CLK_PIN, GPIO_PIN_SET);

    gpio.Pin = CTRL_PWM_MAIN_PIN | LEGACY_V_IN_ON_PIN;
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    gpio.Speed = GPIO_SPEED_FREQ_LOW;
    HAL_GPIO_Init(GPIOA, &gpio);

    gpio.Pin = CTRL_EN_CHG_PIN;
    gpio.Mode = GPIO_MODE_OUTPUT_PP;
    gpio.Pull = GPIO_NOPULL;
    gpio.Speed = GPIO_SPEED_FREQ_LOW;
    HAL_GPIO_Init(GPIOB, &gpio);

    gpio.Pin = FAULT_OCP_PIN | FAULT_OVP_PIN;
    gpio.Mode = GPIO_MODE_INPUT;
    gpio.Pull = GPIO_NOPULL;
    HAL_GPIO_Init(GPIOB, &gpio);
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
